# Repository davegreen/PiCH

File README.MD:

Readme - PiCH
====================

Description
---------------------

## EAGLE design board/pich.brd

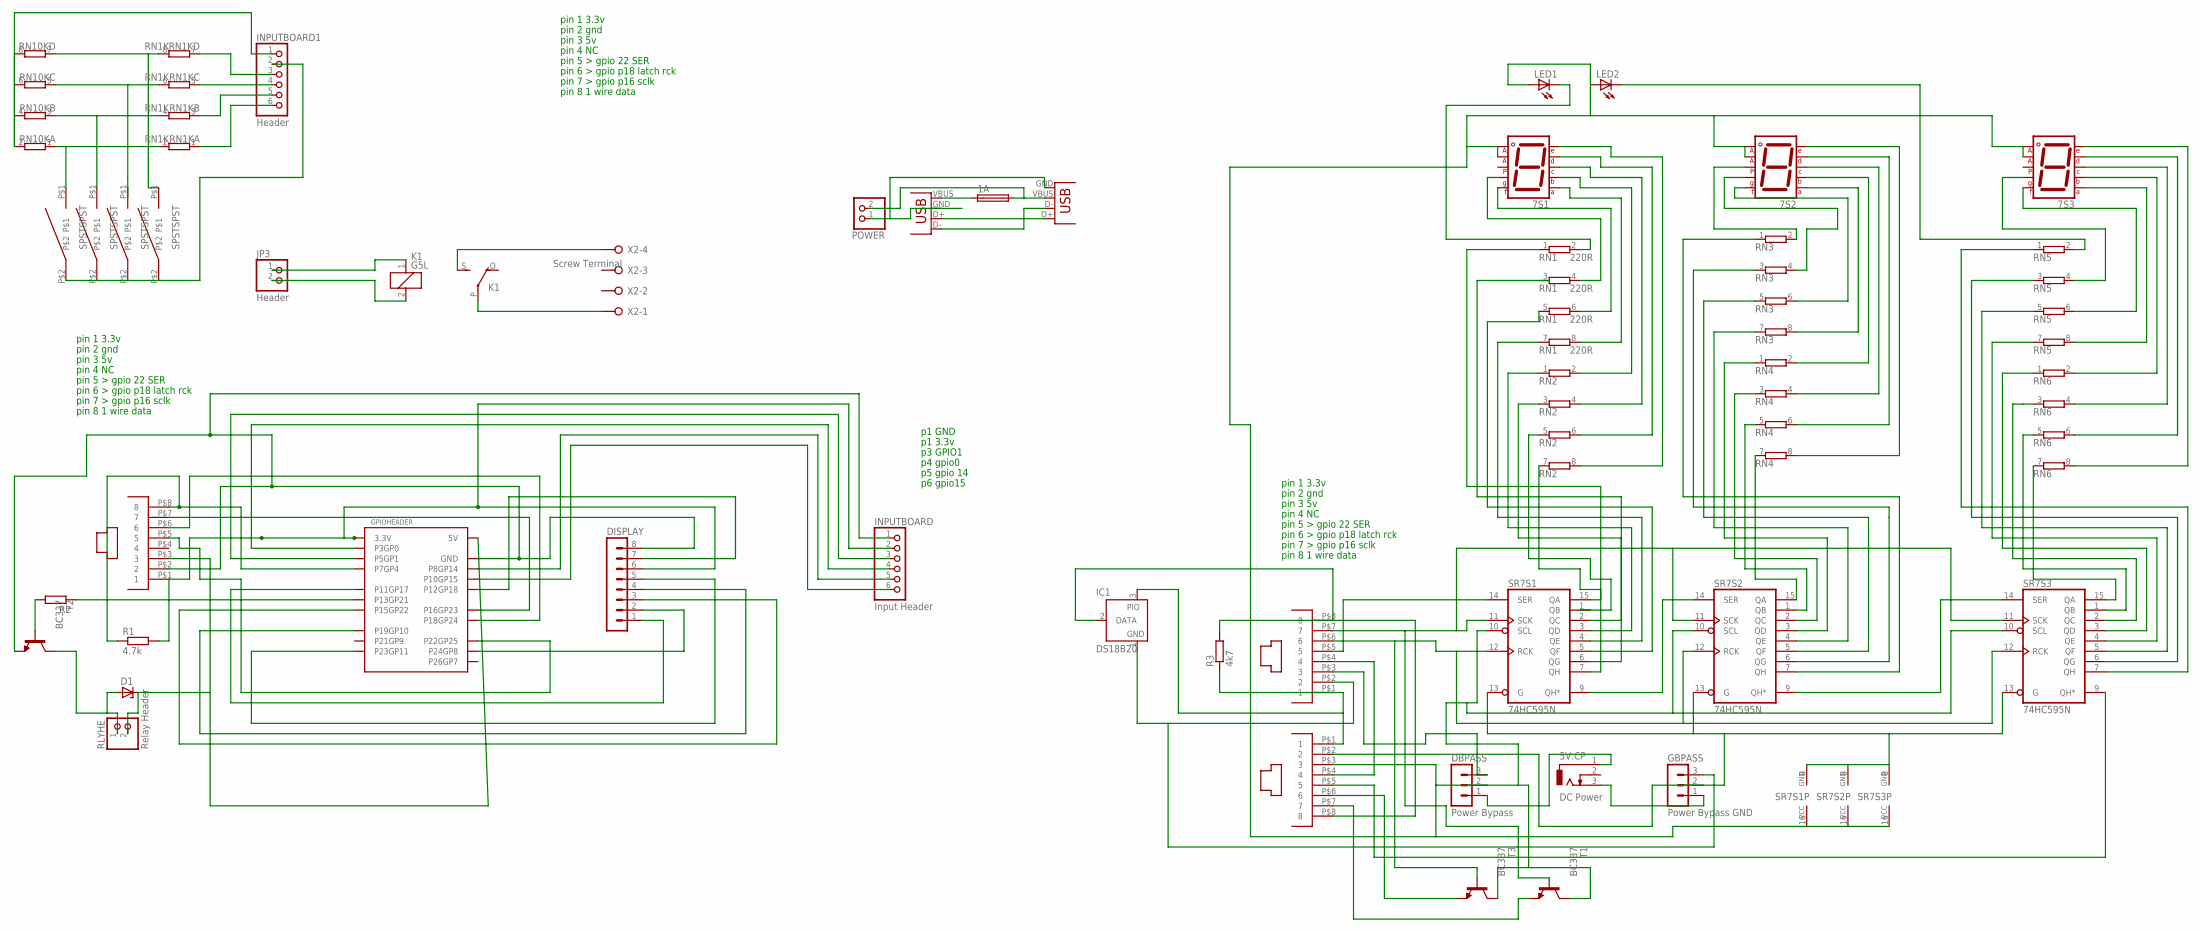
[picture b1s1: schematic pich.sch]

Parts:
1A: QPL
5V.CP: DC Power; DCJ0303
7S1, 7S2, 7S3: 7SEG-MCA; 7SEG-7
.: USB-A-H
D1: 1N821; DO35Z10
DBPASS: Power Bypass; MA03-1
DISPLAY: MA08-1
GBPASS: Power Bypass GND; MA03-1
GPIOHEADER: GPIOGPIOHEADER; FE13-2
IC1: DS18B20; TO92-
INPUTBOARD: Input Header; 1X06
INPUTBOARD1: Header; 1X06
INPUTHEADER: ETHERNETTRUCONNECTRAPID; ETHERNET
JP3: Header; 1X02
K1: G5L; G5LE
LED1, LED2: LED3MM
OUTPUTHEADER: ETHERNETTRUCONNECTRAPID; ETHERNET
POWER: PINHD-1X2; 1X02
R1: 4.7k; 0207/10
R2: R-EU_0204/7; 0204/7
R3: 4k7; 0204V
RLYHE: Relay Header; 1X02
RN1: 220R; SIL8
RN1K: RN1K; SIL8
RN2, RN3, RN4, RN5, RN6: E4RP; SIL8
RN10K: E4R; SIL8
SR7S1, SR7S2, SR7S3: 74HC595N; DIL16
T1, T2, T3: BC337; TO92
THERMHEADER: ETHERNETTRUCONNECTRAPID; ETHERNET
U$2, U$3, U$4, U$5: SPSTSPST; MAPLINSWITCH
X1: USB-A-HU
X2: Screw Terminal; W237-4P

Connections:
GND: DISPLAY.8, GPIOHEADER.6 (GND), GPIOHEADER.9 (GND), GPIOHEADER.14 (GND), GPIOHEADER.20 (GND), GPIOHEADER.25 (GND), INPUTBOARD.1, T2.1 (E), THERMHEADER.P$2 (2)
GND1: ..GND (VBUS), POWER.1, X1.GND
GPIO4W1DATA: GPIOHEADER.7 (P7GP4), R1.1, THERMHEADER.P$8 (8)
unnamed: 1A.2, POWER.2, X1.VBUS
unnamed: D1.C, GPIOHEADER.2 (5V), GPIOHEADER.4 (5V), RLYHE.2, THERMHEADER.P$3 (3)
unnamed: DISPLAY.7, GPIOHEADER.12 (P12GP18)
unnamed: DISPLAY.1, GPIOHEADER.11 (P11GP17)
unnamed: DISPLAY.5, GPIOHEADER.23 (P23GP11)
unnamed: DISPLAY.4, GPIOHEADER.19 (P19GP10)
unnamed: DISPLAY.3, GPIOHEADER.15 (P15GP22)
unnamed: DISPLAY.2, GPIOHEADER.24 (P24GP8)
unnamed: GPIOHEADER.16 (P16GP23), THERMHEADER.P$7 (7)
unnamed: GPIOHEADER.18 (P18GP24), THERMHEADER.P$6 (6)
unnamed: GPIOHEADER.22 (P22GP25), THERMHEADER.P$5 (5)
unnamed: D1.A, RLYHE.1, T2.3 (C)
unnamed: GPIOHEADER.13 (P13GP21), R2.1
unnamed: R2.2, T2.2 (B)
unnamed: JP3.1, K1.1
unnamed: JP3.2, K1.2
unnamed: GPIOHEADER.3 (P3GP0), INPUTBOARD.4
unnamed: GPIOHEADER.8 (P8GP14), INPUTBOARD.5
unnamed: GPIOHEADER.5 (P5GP1), INPUTBOARD.3
unnamed: GPIOHEADER.10 (P10GP15), INPUTBOARD.6
unnamed: K1.P, X2.1
unnamed: K1.S, X2.4
unnamed: SR7S1.9 (QH*), SR7S2.14 (SER)
unnamed: IC1.3 (PIO), INPUTHEADER.P$1 (1), OUTPUTHEADER.P$1 (1), R3.1
unnamed: GBPASS.2, OUTPUTHEADER.P$2 (2), SR7S1.8 (GND), SR7S1.13 (G), SR7S2.8 (GND), SR7S2.13 (G), SR7S3.8 (GND), SR7S3.13 (G)
unnamed: INPUTHEADER.P$4 (4), OUTPUTHEADER.P$4 (4)
unnamed: INPUTHEADER.P$5 (5), SR7S1.14 (SER)
unnamed: INPUTHEADER.P$6 (6), SR7S1.12 (RCK), SR7S2.12 (RCK), SR7S3.12 (RCK), T3.2 (B)
unnamed: IC1.2 (DATA), INPUTHEADER.P$8 (8), OUTPUTHEADER.P$8 (8), R3.2
unnamed: SR7S2.9 (QH*), SR7S3.14 (SER)
unnamed: LED1.K (C), RN1.2
unnamed: 7S1.3 (G), RN1.4 (2)
unnamed: 7S1.2 (F), RN1.6 (2)
unnamed: 7S1.10 (A), RN1.8 (2)
unnamed: 7S1.9 (B), RN2.2
unnamed: 7S1.8 (C), RN2.4 (2)
unnamed: 7S1.5 (D), RN2.6 (2)
unnamed: 7S1.4 (E), RN2.8 (2)
unnamed: RN2.7 (1), SR7S1.15 (QA)
unnamed: RN2.5 (1), SR7S1.1 (QB)
unnamed: RN2.3 (1), SR7S1.2 (QC)
unnamed: RN2.1, SR7S1.3 (QD)
unnamed: RN1.7 (1), SR7S1.4 (QE)
unnamed: RN1.5 (1), SR7S1.5 (QF)
unnamed: RN1.3 (1), SR7S1.6 (QG)
unnamed: RN1.1, SR7S1.7 (QH)
unnamed: GBPASS.3, IC1.1 (GND), INPUTHEADER.P$2 (2)
unnamed: 7S2.7 (DP), RN3.2
unnamed: 7S2.3 (G), RN3.4 (2)
unnamed: 7S2.2 (F), RN3.6 (2)
unnamed: 7S2.10 (A), RN3.8 (2)
unnamed: 7S2.9 (B), RN4.2
unnamed: 7S2.8 (C), RN4.4 (2)
unnamed: 7S2.5 (D), RN4.6 (2)
unnamed: 7S2.4 (E), RN4.8 (2)
unnamed: RN4.7 (1), SR7S2.15 (QA)
unnamed: RN4.5 (1), SR7S2.1 (QB)
unnamed: RN4.1, SR7S2.3 (QD)
unnamed: RN3.7 (1), SR7S2.4 (QE)
unnamed: RN3.3 (1), SR7S2.6 (QG)
unnamed: RN3.1, SR7S2.7 (QH)
unnamed: LED2.K (C), RN5.2
unnamed: 7S3.3 (G), RN5.4 (2)
unnamed: 7S3.2 (F), RN5.6 (2)
unnamed: 7S3.10 (A), RN5.8 (2)
unnamed: 7S3.9 (B), RN6.2
unnamed: 7S3.8 (C), RN6.4 (2)
unnamed: 7S3.5 (D), RN6.6 (2)
unnamed: 7S3.4 (E), RN6.8 (2)
unnamed: RN6.7 (1), SR7S3.15 (QA)
unnamed: RN6.5 (1), SR7S3.1 (QB)
unnamed: RN6.3 (1), SR7S3.2 (QC)
unnamed: RN6.1, SR7S3.3 (QD)
unnamed: RN5.7 (1), SR7S3.4 (QE)
unnamed: RN5.5 (1), SR7S3.5 (QF)
unnamed: RN5.3 (1), SR7S3.6 (QG)
unnamed: RN5.1, SR7S3.7 (QH)
unnamed: DBPASS.3, INPUTHEADER.P$3 (3)
unnamed: RN4.3 (1), SR7S2.2 (QC)
unnamed: RN3.5 (1), SR7S2.5 (QF)
unnamed: 5V.CP.1, DBPASS.1
unnamed: 5V.CP.3, GBPASS.1
unnamed: 7S1.1 (CA1), 7S1.6 (CA2), 7S2.1 (CA1), 7S2.6 (CA2), 7S3.1 (CA1), 7S3.6 (CA2), DBPASS.2, LED1.A, LED2.A, OUTPUTHEADER.P$3 (3), SR7S1.10 (SCL), SR7S1.16 (VCC), SR7S2.10 (SCL), SR7S2.16 (VCC), SR7S3.10 (SCL), SR7S3.16 (VCC), T1.3 (C), T3.3 (C)
unnamed: OUTPUTHEADER.P$5 (5), SR7S3.9 (QH*)
unnamed: 1A.1, ..VBUS (GND)
unnamed: ..D- (D+), X1.D-
unnamed: ..D+ (D-), X1.D+
unnamed: OUTPUTHEADER.P$7 (7), T1.1 (E)
unnamed: RN1K.8 (2), RN10K.7 (1), U$5.P$1
unnamed: INPUTBOARD1.1, RN10K.2, RN10K.4 (2), RN10K.6 (2), RN10K.8 (2)
unnamed: INPUTBOARD1.3, RN1K.7 (1)
unnamed: INPUTBOARD1.4, RN1K.5 (1)
unnamed: INPUTBOARD1.5, RN1K.3 (1)
unnamed: INPUTBOARD1.6, RN1K.1
unnamed: INPUTBOARD1.2, U$2.P$2, U$3.P$2, U$4.P$2, U$5.P$2
unnamed: RN1K.6 (2), RN10K.5 (1), U$4.P$1
unnamed: RN1K.4 (2), RN10K.3 (1), U$3.P$1
unnamed: RN1K.2, RN10K.1, U$2.P$1
unnamed: INPUTHEADER.P$7 (7), SR7S1.11 (SCK), SR7S2.11 (SCK), SR7S3.11 (SCK), T1.2 (B)
unnamed: OUTPUTHEADER.P$6 (6), T3.1 (E)
VCC: DISPLAY.6, GPIOHEADER.1 (3.3V), GPIOHEADER.17 (3.3V), INPUTBOARD.2, R1.2, THERMHEADER.P$1 (1)

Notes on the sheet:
pin 1 3.3v
pin 2 gnd
pin 3 5v
pin 4 NC
pin 5 > gpio 22 SER
pin 6 > gpio p18 latch rck
pin 7 > gpio p16 sclk
pin 8 1 wire data
p1 GND
p1 3.3v
p3 GPIO1
p4 gpio0
p5 gpio 14
p6 gpio15

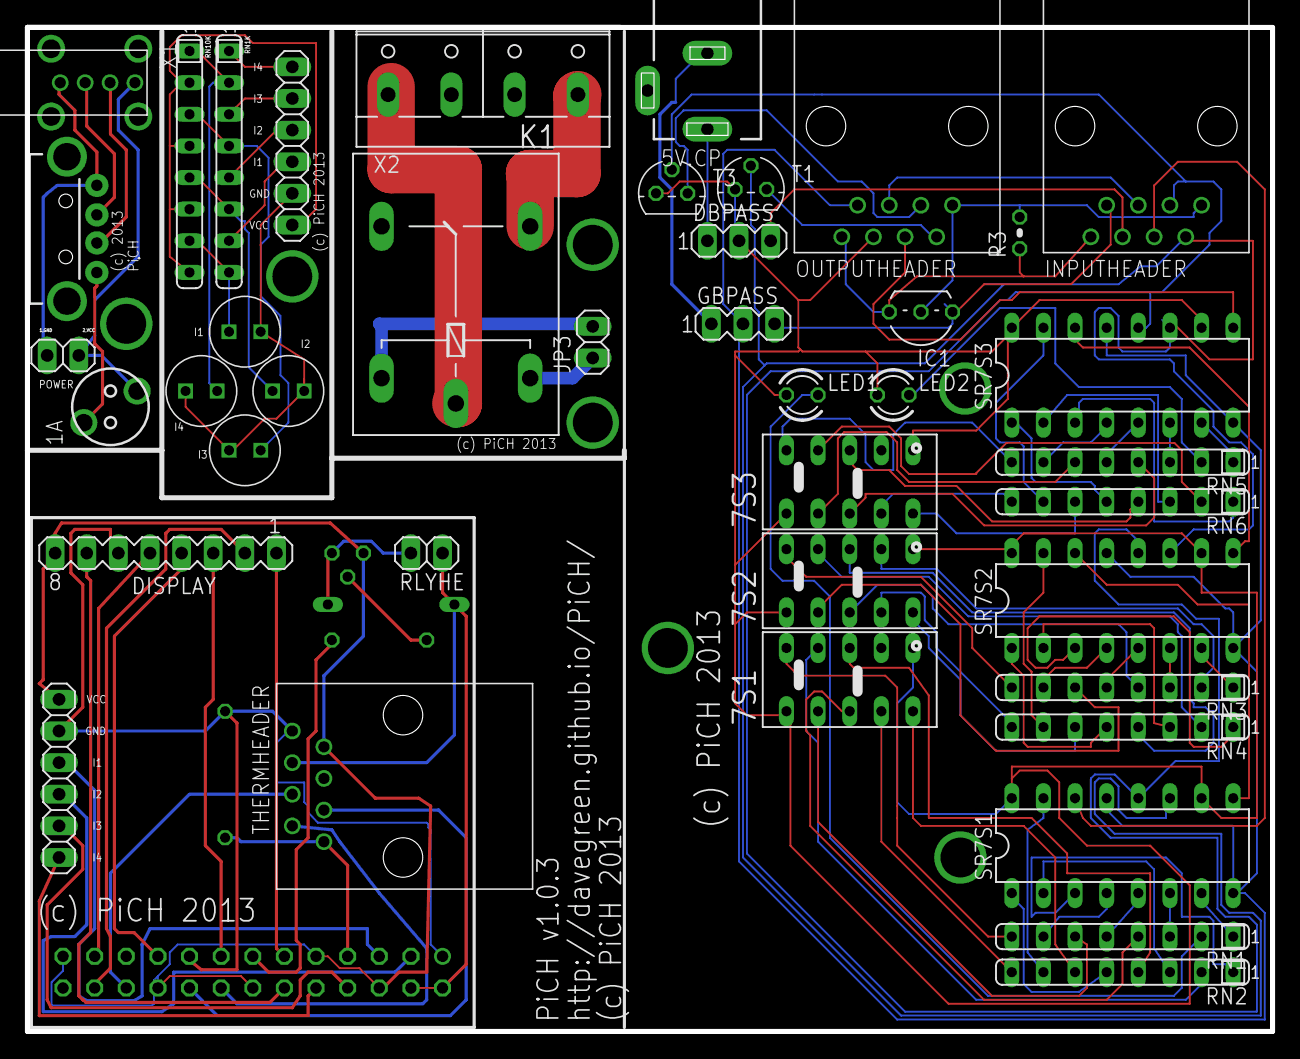
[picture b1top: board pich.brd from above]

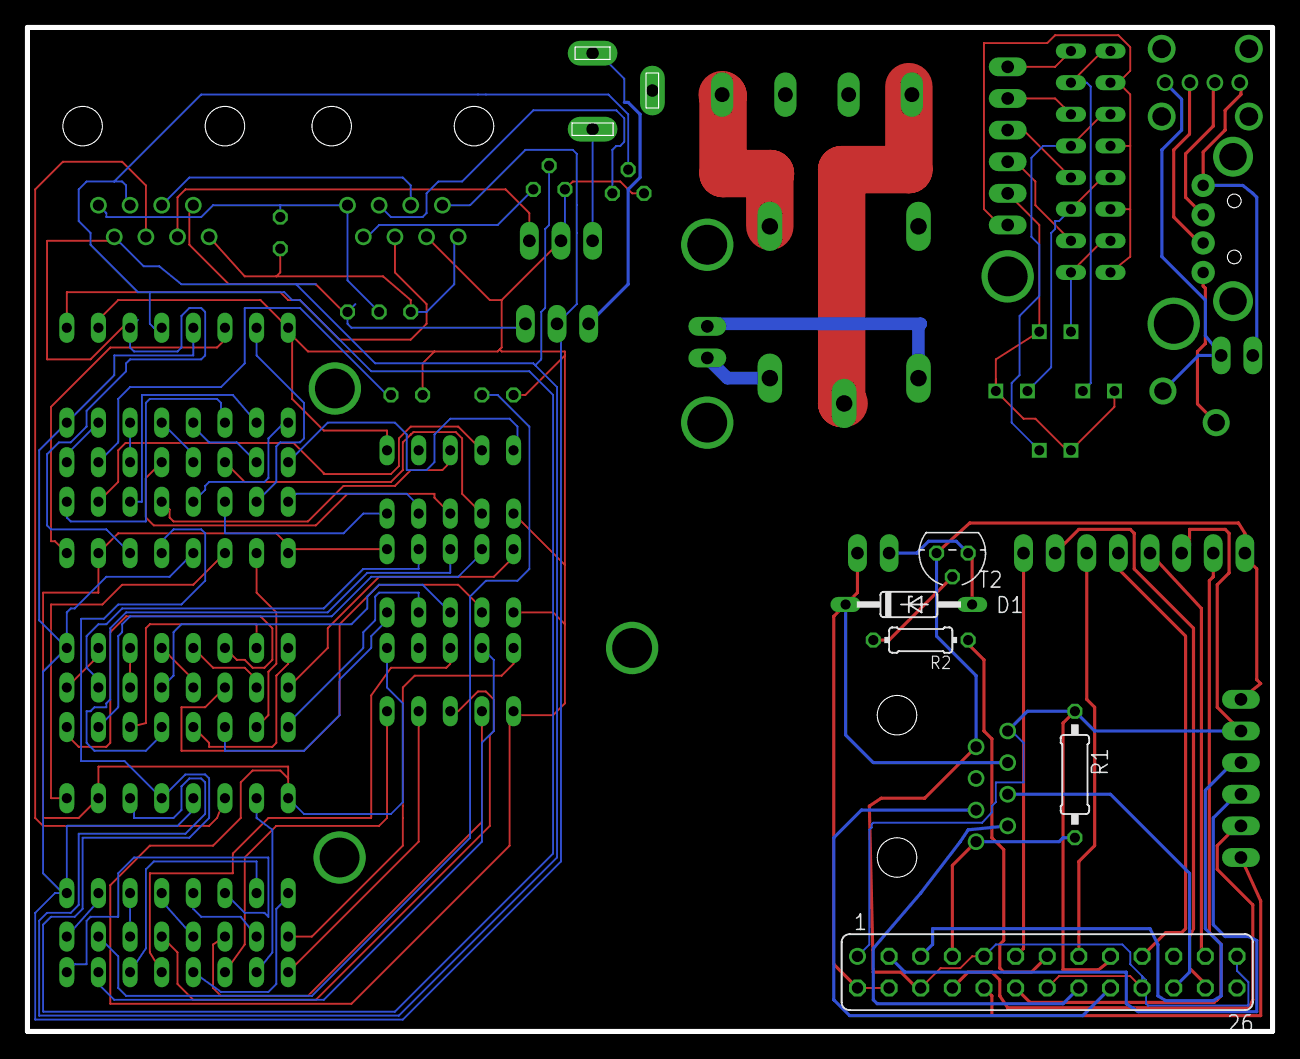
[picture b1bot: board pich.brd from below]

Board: 4 copper layers, 100.0 x 80.6 mm, 46 parts (5 on the bottom side), 104 nets.

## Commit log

2013-12-13 Initial README
2013-12-13 Lets try this again, shall we?
2013-12-13 More README to read.
2013-12-13 Initial commit of test scripts for the 7 segment display hardware.
2013-12-13 Initial commit of the web interface
2013-12-13 Add TODO list
2013-12-13 Add initial setup
2013-12-13 Improve README
2013-12-13 Step to add 1-wire bus modules to /etc/modules so that things work on boot
2013-12-13 Add comments for module loading on startup.
2013-12-14 Update Bootstrap
    Still needs a lot of work. lots of stuff unstyled.
2013-12-14 Update status page.
2013-12-14 Correct header navbar class
2013-12-14 Move heating on/off notification to the navbar
2013-12-14 Complete moving on/off notification
2013-12-14 Initial thanks
2013-12-14 Partially improve status page layout
2013-12-14 Include container <div>
2013-12-14 Refactor sensor display/settings page
2013-12-14 Add watchdog.py
2013-12-14 Add thermostat.py/.sh for schedule control
2013-12-14 Add settings.py
2013-12-14 Add killtherm.py/.sh for schedule termination
2013-12-15 Add .gitattributes and .gitignore
2013-12-15 Create gh-pages branch via GitHub
2013-12-15 Improve setup script
2013-12-23 Add templog.png
2013-12-23 Add templog image to main page.
2013-12-23 Re-add templog image.
2013-12-23 Update title.
2013-12-29 Update thermostat.py
    Add update to status table
2013-12-29 First public release of PiCH boards
2013-12-29 Update folder structure
2013-12-29 Correct indenting and remove copied comment.
2014-01-02 Add temperature logging page image
2014-01-04 Move sleep to correct place and change to 60 seconds
2014-01-04 Comment sleep
2014-01-04 Testing file permissions
2014-01-04 File permissions for all executables
2014-01-04 Thermostat script now looks for argument 2
2014-01-04 Now reads current temp from SQL
2014-01-04 Case sensitive web address
2014-01-04 Add running board images
2014-01-04 Update setup instructions
2014-01-09 Added board images
2014-01-09 Add Running section.
2014-01-12 Added loadaverages logging
2014-01-12 Added stats table
2018-01-17 Correct images

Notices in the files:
board/pich.brd:
(c) 2013
parts and their libraries:
SparkFun-Connectors: Licensing: CC v3.0 Share-Alike You are welcome to use this library for commercial purposes.
